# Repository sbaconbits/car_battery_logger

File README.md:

# car_battery_logger
A microcontroller project to log car battery power usage.
For more information see my blog posts on this project http://www.firmic-designs.com/blog/categories/car-battery-logger/

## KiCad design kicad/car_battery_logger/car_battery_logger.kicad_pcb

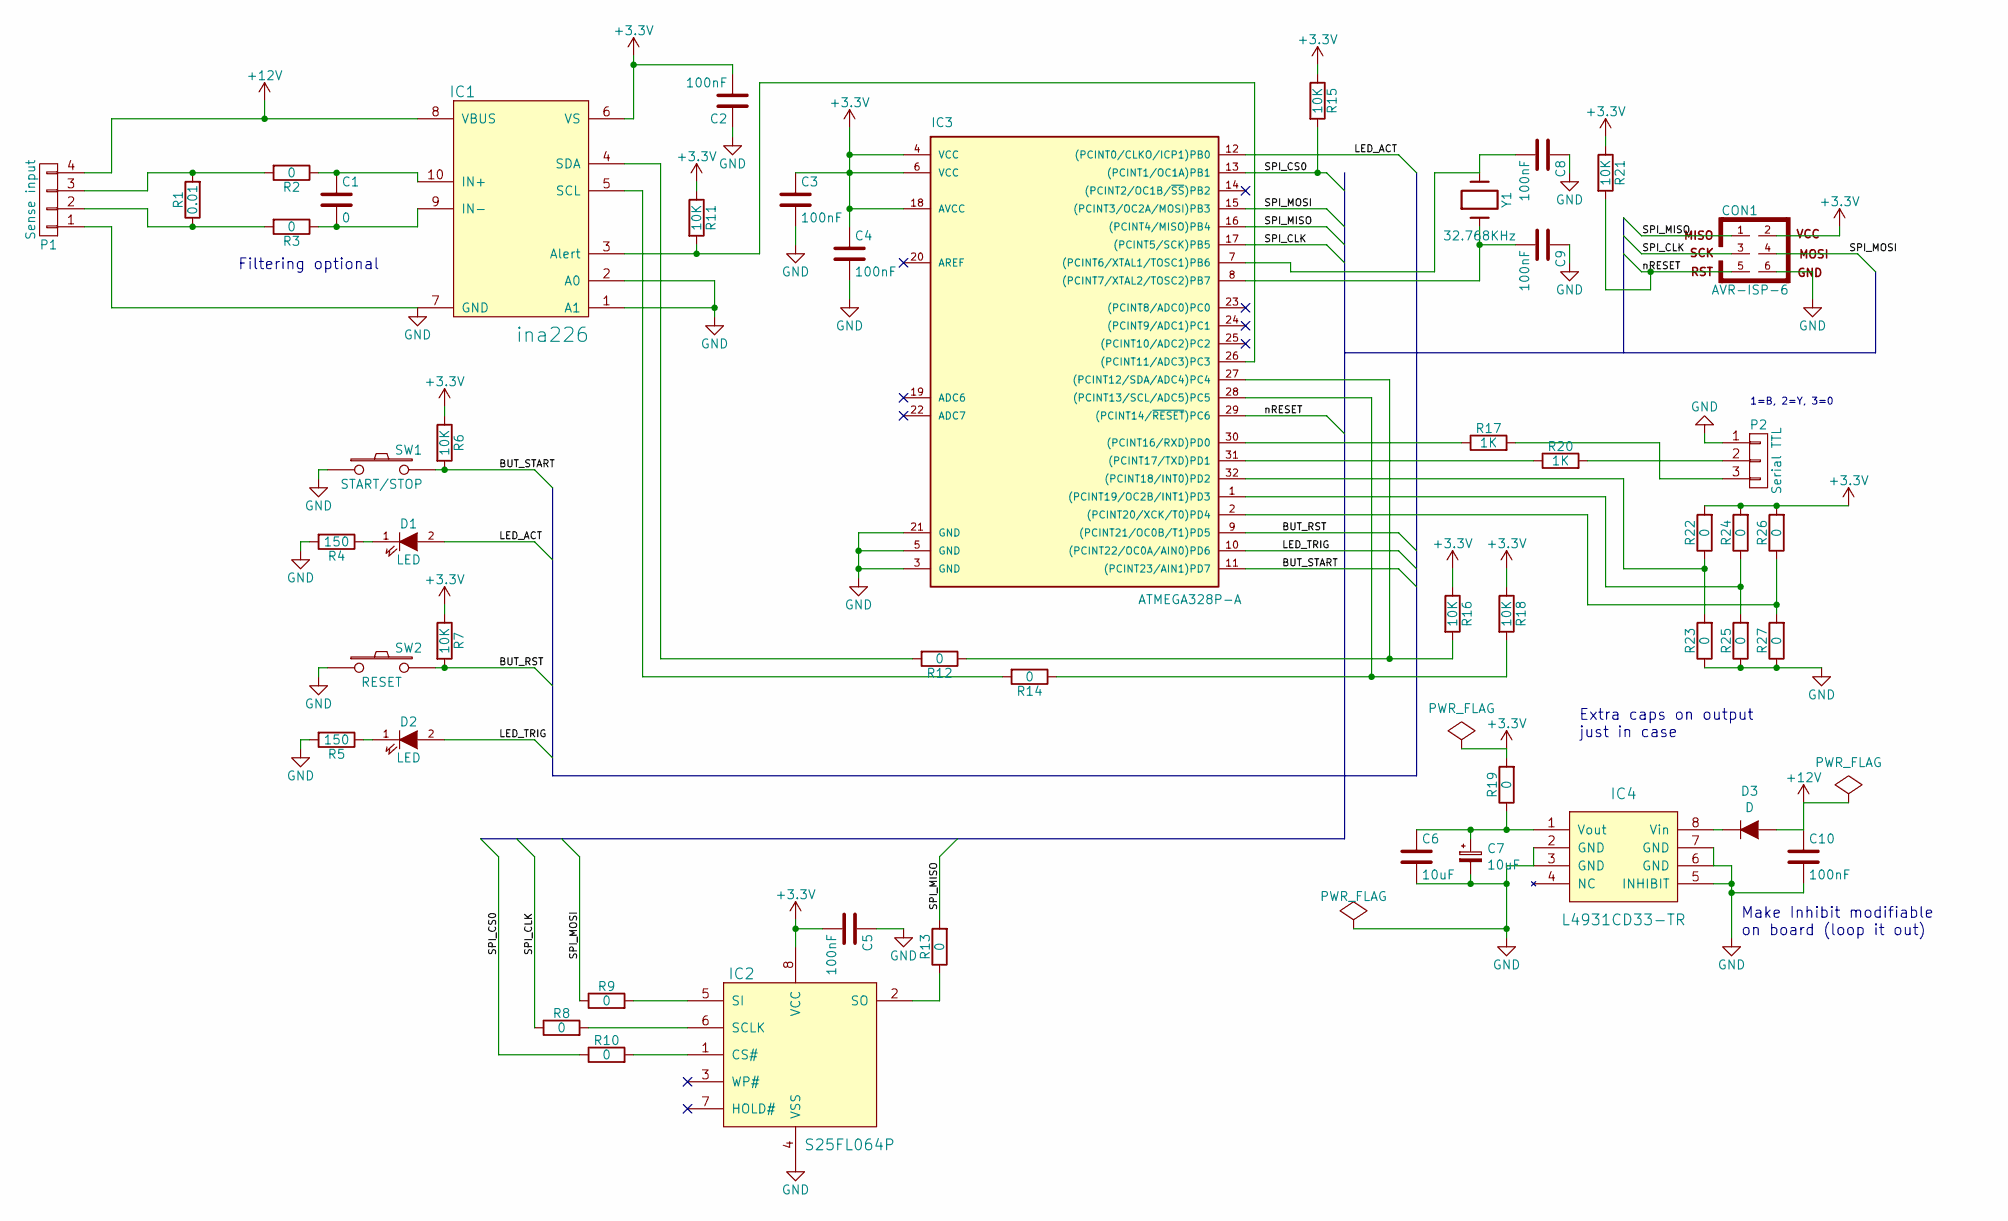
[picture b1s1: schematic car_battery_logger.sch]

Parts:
C1: 0; C_0805_HandSoldering
C2, C3, C4, C5, C8, C9, C10: 100nF; C_0805_HandSoldering
C6: 10uF; C_1206_HandSoldering
C7: 10uF; C_Radial_D5_L11_P2
CON1: AVR-ISP-6; AVR_ISP_HEADER_6PIN
D1, D2: LED; LED-5MM
D3: D; SMA_Handsoldering
IC1: ina226; TSSOP-10_3x3mm_Pitch0.5mm_big_foot
IC2: S25FL064P; SOC008_5.3x5.3mm_Pitch1.27mm_big_foot
IC3: ATMEGA328P-A; TQFP-32_7x7mm_Pitch0.8mm_big_foot
IC4: L4931CD33-TR; SOIC-8_3.9x4.9mm_Pitch1.27mm_big_foot
P1: Sense input; GPIO_header_1x4
P2: Serial TTL; Serial_header
R1: 0.01; R_2512_HandSoldering
R2, R3, R8, R9, R10, R12, R13, R14, R19, R22, R23, R24, R25, R26, R27: 0; R_0805_HandSoldering
R4, R5: 150; R_0805_HandSoldering
R6, R7, R11, R15, R16, R18, R21: 10K; R_0805_HandSoldering
R17, R20: 1K; R_0805_HandSoldering
SW1: START/STOP; Button_connector
SW2: RESET; Button_connector
Y1: 32.768KHz; Crystal_Round_Horizontal_2mm

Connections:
+3V3: C2.2, C3.1, C4.1, C5.2, CON1.2, IC1.6 (VS), IC2.8 (VCC), IC3.4 (VCC), IC3.6 (VCC), IC3.18 (AVCC), R6.1, R7.1, R11.1, R15.1, R16.1, R18.1, R19.2, R21.1, R22.2, R24.2, R26.2
+12V: C10.1, D3.2 (A), IC1.8 (VBUS), P1.4
/BUT_RST: IC3.9 ((PCINT21/OC0B/T1)PD5), R7.2, SW2.2
/BUT_START: IC3.11 ((PCINT23/AIN1)PD7), R6.2, SW1.2
/LED_ACT: D1.2 (A), IC3.12 ((PCINT0/CLKO/ICP1)PB0)
/LED_TRIG: D2.2 (A), IC3.10 ((PCINT22/OC0A/AIN0)PD6)
/SPI_CLK: CON1.3, IC3.17 ((PCINT5/SCK)PB5), R8.1
/SPI_CS0: IC3.13 ((PCINT1/OC1A)PB1), R10.1, R15.2
/SPI_MISO: CON1.1, IC3.16 ((PCINT4/MISO)PB4), R13.2
/SPI_MOSI: CON1.4, IC3.15 ((PCINT3/OC2A/MOSI)PB3), R9.1
/nRESET: CON1.5, IC3.29 ((PCINT14/~RESET~)PC6), R21.2
GND: C2.1, C3.2, C4.2, C5.1, C6.2, C7.2, C8.1, C9.1, C10.2, CON1.6, IC1.1 (A1), IC1.2 (A0), IC1.7 (GND), IC2.4 (VSS), IC3.3 (GND), IC3.5 (GND), IC3.21 (GND), IC4.2 (GND), IC4.3 (GND), IC4.5 (INHIBIT), IC4.6 (GND), IC4.7 (GND), P1.1, P2.1, R4.2, R5.2, R23.1, R25.1, R27.1, SW1.1, SW2.1
unnamed: C1.1, IC1.10 (IN+), R2.1
unnamed: C1.2, IC1.9 (IN-), R3.1
unnamed: C6.1, C7.1, IC4.1 (Vout), R19.1
unnamed: C8.2, IC3.7 ((PCINT6/XTAL1/TOSC1)PB6), Y1.2
unnamed: C9.2, IC3.8 ((PCINT7/XTAL2/TOSC2)PB7), Y1.1
unnamed: D1.1 (K), R4.1
unnamed: D2.1 (K), R5.1
unnamed: D3.1 (K), IC4.8 (Vin)
unnamed: IC1.3 (Alert), IC3.26 ((PCINT11/ADC3)PC3), R11.2
unnamed: IC1.4 (SDA), R12.2
unnamed: IC1.5 (SCL), R14.2
unnamed: IC2.1 (CS#), R10.2
unnamed: IC2.2 (SO), R13.1
unnamed: IC2.5 (SI), R9.2
unnamed: IC2.6 (SCLK), R8.2
unnamed: IC3.1 ((PCINT19/OC2B/INT1)PD3), R24.1, R25.2
unnamed: IC3.2 ((PCINT20/XCK/T0)PD4), R26.1, R27.2
unnamed: IC3.27 ((PCINT12/SDA/ADC4)PC4), R12.1, R16.2
unnamed: IC3.28 ((PCINT13/SCL/ADC5)PC5), R14.1, R18.2
unnamed: IC3.30 ((PCINT16/RXD)PD0), R17.1
unnamed: IC3.31 ((PCINT17/TXD)PD1), R20.1
unnamed: IC3.32 ((PCINT18/INT0)PD2), R22.1, R23.2
unnamed: P1.2, R1.1, R3.2
unnamed: P1.3, R1.2, R2.2
unnamed: P2.2, R20.2
unnamed: P2.3, R17.2

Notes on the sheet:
Make Inhibit modifiable on board (loop it out)
Extra caps on output just in case
Filtering optional
1=B, 2=Y, 3=0

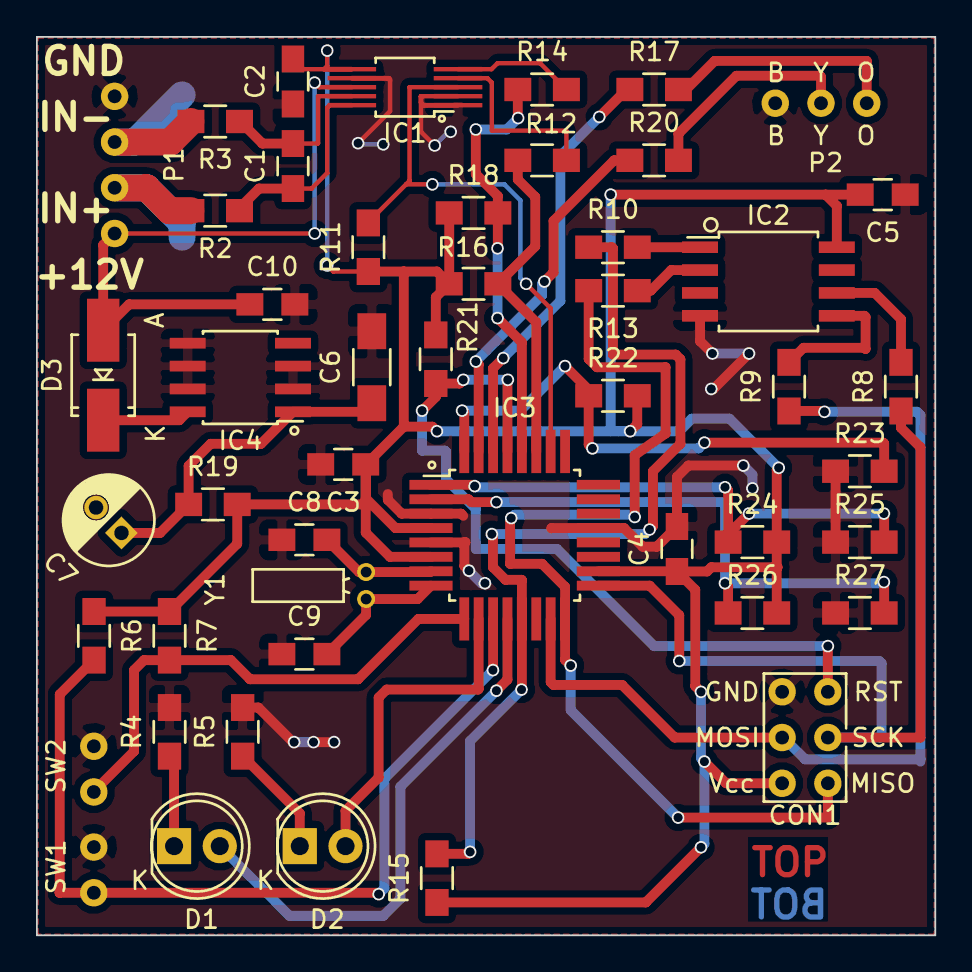
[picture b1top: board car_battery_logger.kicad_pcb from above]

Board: 2 copper layers, 49.9 x 49.9 mm, 50 parts (1 on the bottom side), 38 nets.

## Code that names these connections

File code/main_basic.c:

// Copyright (c) 2016 Steven Bacon
//
// Permission is hereby granted, free of charge, to any person obtaining a copy of
// this software and associated documentation files (the "Software"), to deal in
// the Software without restriction, including without limitation the rights to
// use, copy, modify, merge, publish, distribute, sublicense, and/or sell copies
// of the Software, and to permit persons to whom the Software is furnished to do
// so, subject to the following conditions:
//
// The above copyright notice and this permission notice shall be included in all
// copies or substantial portions of the Software.
//
// THE SOFTWARE IS PROVIDED "AS IS", WITHOUT WARRANTY OF ANY KIND, EXPRESS OR
// IMPLIED, INCLUDING BUT NOT LIMITED TO THE WARRANTIES OF MERCHANTABILITY,
// FITNESS FOR A PARTICULAR PURPOSE AND NONINFRINGEMENT. IN NO EVENT SHALL THE
// AUTHORS OR COPYRIGHT HOLDERS BE LIABLE FOR ANY CLAIM, DAMAGES OR OTHER
// LIABILITY, WHETHER IN AN ACTION OF CONTRACT, TORT OR OTHERWISE, ARISING FROM,
// OUT OF OR IN CONNECTION WITH THE SOFTWARE OR THE USE OR OTHER DEALINGS IN THE
// SOFTWARE.
//
// File Name: main_basic.c
//
#include <avr/io.h>
#include <util/delay.h>
#include <avr/interrupt.h>
#include <avr/pgmspace.h>
//#include <avr/wdt.h>
#include <inttypes.h>

#include "serial.h"

//PB1 flash CS#
//ina226 alert PC3


// /usr/lib/avr/include/avr

//      Atmega328p pinout
//          ---------
//      PC6 | 1   28| PC5
//  RXD PD0 | 2   27| PC4
//  TXD PD1 | 3   26| PC3
//      PD2 | 4   25| PC2
//      PD3 | 5   24| PC1
//      PD4 | 6   23| PC0
//      VCC | 7   22| GND
//      GND | 8   21| AREF
//      PB6 | 9   20| AVCC
//      PB7 |10   19| PB5   (SCK  - spi clock)
//      PD5 |11   18| PB4   (MISO - SPI master input / slave output)
//      PD6 |12   17| PB3   (MOSI - SPI master output / slave input)
//      PD7 |13   16| PB2   (SS   - SPI slave select)
//      PB0 |14   15| PB1   SPI_FLASH_N_CS
//          ---------

void init(void)
{
    //TODO hw_init()

    PORTB = 0x00;
    // PB0, PB1 output
    DDRB |= (1 << DDB0);
    DDRB |= (1 << DDB1);

    // PC5 output
    DDRC |= (1 << DDC5);

    // PD6 output
    DDRD |= (1 << DDD6);

    // PD7 input
    DDRD &= ~(1 << DDD7);

    //Clock prescale register
    CLKPR = 0x0; //clk_io = F_CPU (no scaling)


}

#define LED_ACT_ON          (PORTB |=  (1 << PB0))
#define LED_ACT_OFF         (PORTB &= ~(1 << PB0))
#define LED_ACT_TOGGLE      (PORTB ^=  (1 << PB0))

#define LED_TRG_ON          (PORTD |=  (1 << PD6))
#define LED_TRG_OFF         (PORTD &= ~(1 << PD6))
#define LED_TRG_TOGGLE      (PORTD ^=  (1 << PD6))

volatile uint32_t secs = 0;
ISR (TIMER2_OVF_vect, ISR_BLOCK)
{
    secs++;
    LED_TRG_TOGGLE;
    //LED_ACT_TOGGLE;
}

void rtc_init(void)
{
    // Crystal = 32.768KHz (pow(2,15)/sec)
    // pow(2,15) = pow(2,7) * pow(2,8)
    // 32768 = 128 * 256.

    // Timer 2

    // Asynchronous Timer/Counter2
    // Setting this can corrupt the following registers.
    ASSR = (1 << AS2);

    TCNT2  = 0;
    OCR2A  = 0;
    OCR2B  = 0;
    TCCR2A = 0;

    // mode normal
    // WGM2[2:0] = 000
    // CS2[2:0] = 101
    TCCR2B = (1 << CS22) | (1 << CS20);
    // Timer/Counter overflow interrupt enable
    TIMSK2 = (1 << TOIE2);

    sei(); // Enable interrupts
}

void main_loop(void)
{
    while(1)
    {
        _delay_ms(500);
        LED_ACT_ON;
        _delay_ms(500);
        LED_ACT_OFF;
        uart_hex_32(secs);
        uart_tx_str("\r\n");
    }
}

int main(void)
{
    init();
    uart_init();
    _delay_ms(1000);
    uart_tx_str("Start\r\n");
    rtc_init();
    main_loop();

    return 0;
}

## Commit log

2016-09-02 TEST
2016-09-02 Initial set of files from home.
2016-09-03 Added all of the kicad files.
2016-09-03 Tidy up.
2016-09-10 Added blog text files as backup.
